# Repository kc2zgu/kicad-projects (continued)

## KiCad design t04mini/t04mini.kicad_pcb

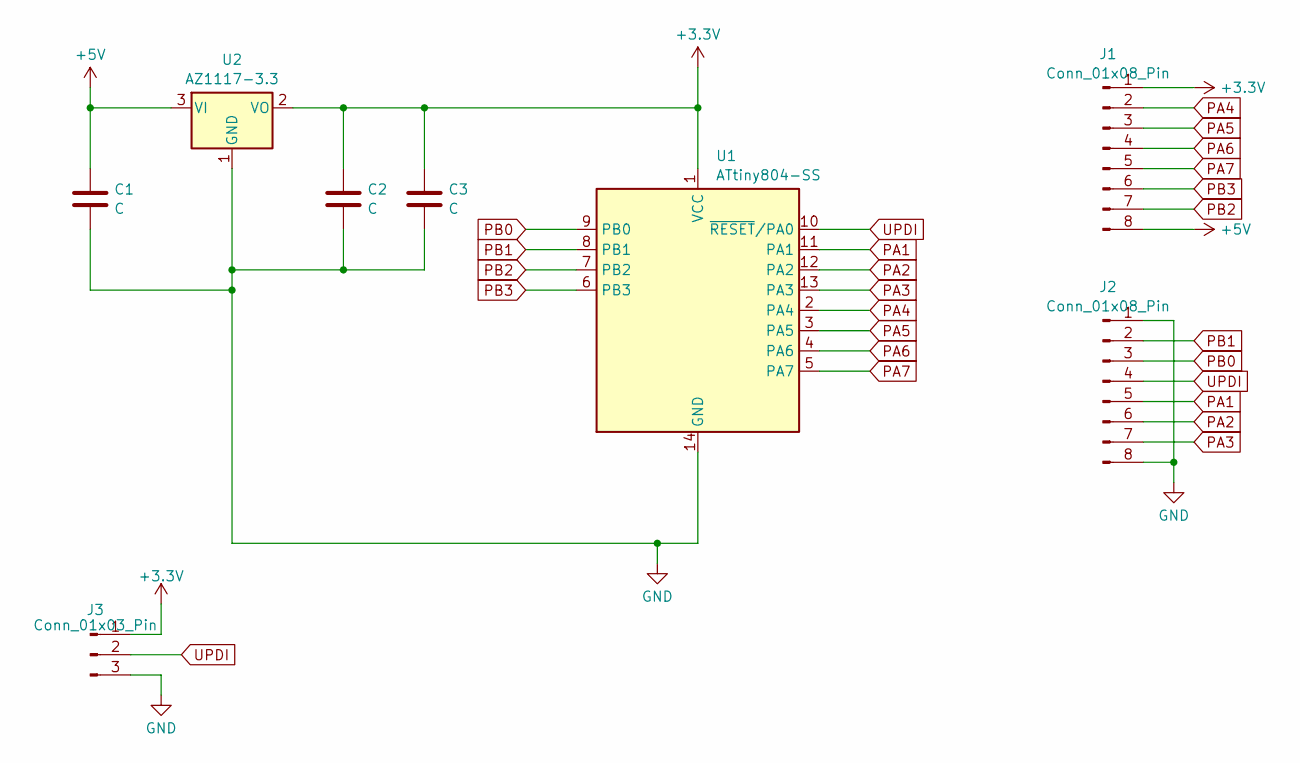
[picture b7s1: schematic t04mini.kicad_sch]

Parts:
C1, C2: C; C_1206_3216Metric
C3: C; C_0805_2012Metric_Pad1.18x1.45mm_HandSolder
J1, J2: Conn_01x08_Pin; PinHeader_1x08_P2.54mm_Vertical
J3: Conn_01x03_Pin; JST_ZH_B3B-ZR_1x03_P1.50mm_Vertical
U1: ATtiny804-SS; SOIC-14_3.9x8.7mm_P1.27mm
U2: AZ1117-3.3; SOT-89-3_Handsoldering

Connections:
+3.3V: C2.1, C3.1, J1.1, J3.1, U1.1 (VCC), U2.2 (VO)
+5V: C1.1, J1.8, U2.3 (VI)
GND: C1.2, C2.2, C3.2, J2.1, J2.8, J3.3, U1.14 (GND), U2.1 (GND)
PA1: J2.5, U1.11 (PA1)
PA2: J2.6, U1.12 (PA2)
PA3: J2.7, U1.13 (PA3)
PA4: J1.2, U1.2 (PA4)
PA5: J1.3, U1.3 (PA5)
PA6: J1.4, U1.4 (PA6)
PA7: J1.5, U1.5 (PA7)
PB0: J2.3, U1.9 (PB0)
PB1: J2.2, U1.8 (PB1)
PB2: J1.7, U1.7 (PB2)
PB3: J1.6, U1.6 (PB3)
UPDI: J2.4, J3.2, U1.10 (~RESET/PA0)

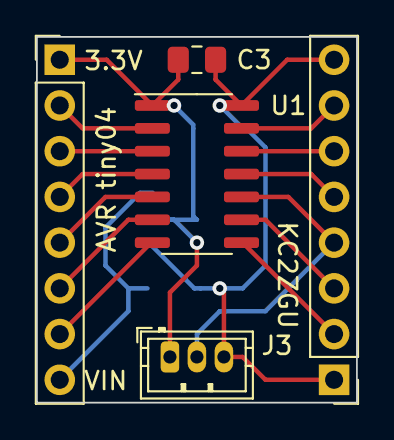
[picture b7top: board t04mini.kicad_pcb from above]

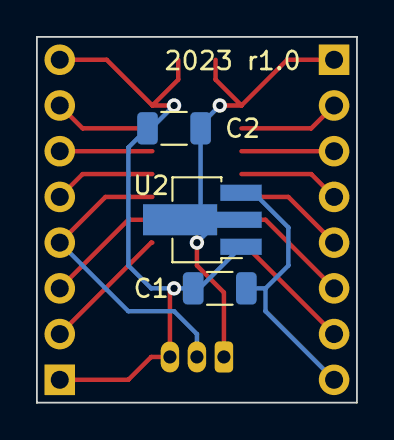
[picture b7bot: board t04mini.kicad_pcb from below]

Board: 2 copper layers, 17.8 x 20.3 mm, 8 parts (3 on the bottom side), 15 nets.

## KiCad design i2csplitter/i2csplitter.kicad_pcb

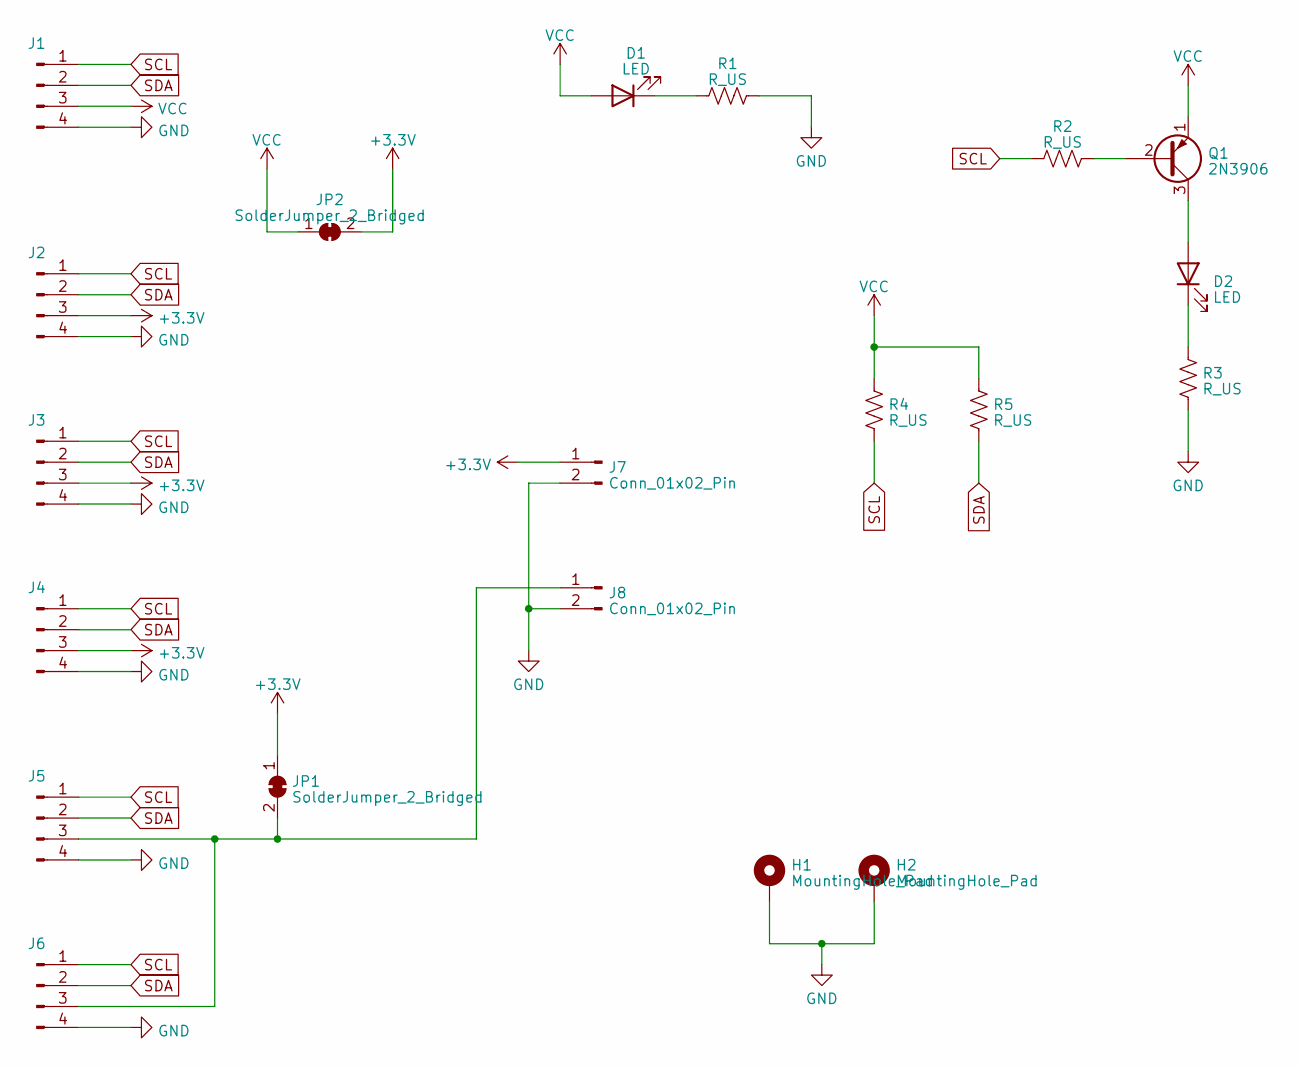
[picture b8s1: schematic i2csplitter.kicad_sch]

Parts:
D1, D2: LED; LED_D3.0mm
H1, H2: MountingHole_Pad; MountingHole_3.2mm_M3_DIN965_Pad
J1, J2, J3, J4, J5, J6: Conn_01x04_Male; JST_PH_B4B-PH-K_1x04_P2.00mm_Vertical
J7, J8: Conn_01x02_Pin; JST_PH_B2B-PH-K_1x02_P2.00mm_Vertical
JP1, JP2: SolderJumper_2_Bridged; SolderJumper-2_P1.3mm_Bridged_Pad1.0x1.5mm
Q1: 2N3906; TO-92_Inline
R1, R2, R3, R4, R5: R_US; R_0805_2012Metric_Pad1.20x1.40mm_HandSolder

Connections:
+3.3V: J2.3, J3.3, J4.3, J7.1, JP1.1 (A), JP2.2 (B)
GND: H1.1, H2.1, J1.4, J2.4, J3.4, J4.4, J5.4, J6.4, J7.2, J8.2, R1.2, R3.1
unnamed: D1.1 (K), R1.1
unnamed: D2.2 (A), Q1.3 (C)
unnamed: D2.1 (K), R3.2
unnamed: J5.3, J6.3, J8.1, JP1.2 (B)
unnamed: Q1.2 (B), R2.2
SCL: J1.1, J2.1, J3.1, J4.1, J5.1, J6.1, R2.1, R4.1
SDA: J1.2, J2.2, J3.2, J4.2, J5.2, J6.2, R5.1
VCC: D1.2 (A), J1.3, JP2.1 (A), Q1.1 (E), R4.2, R5.2

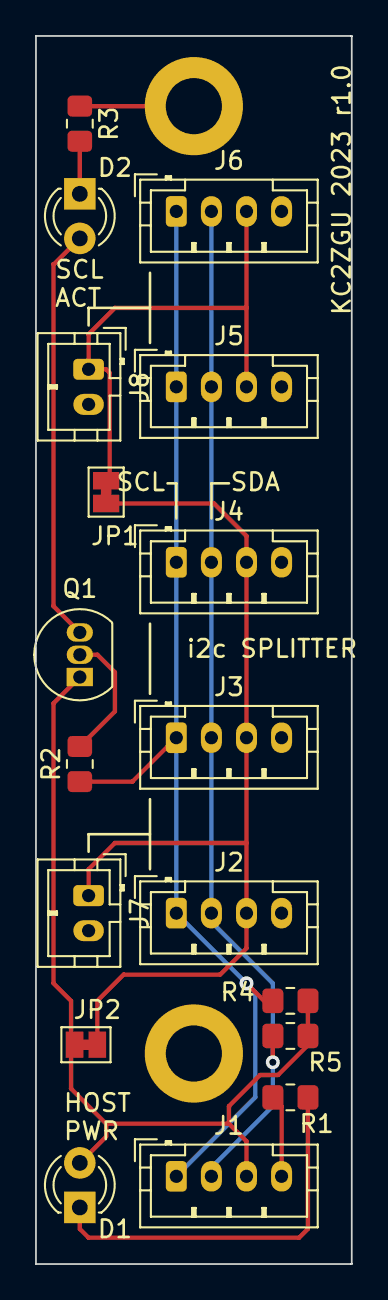
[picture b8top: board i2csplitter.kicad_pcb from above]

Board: 2 copper layers, 18.0 x 70.0 mm, 20 parts (0 on the bottom side), 10 nets.

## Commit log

2024-04-26 [old] mpio8: 8-channel IO board
2024-04-26 [old] hvac-r: relay board for HVAC control
2024-04-26 [old] led-mc-50x16: LED board (metal core design)
2024-04-26 [old] miniald: mini automated light driver (r1.0 fab snapshot)
2024-04-26 [old] mcumod-carrier-breakout: brreakout board for MCUmod
2024-04-26 [old] mcumod-at6: MCUmod for attiny06/16 family
2024-04-26 [old] smartpir: microcontroller-based PIR light driver
2024-04-26 [old] miniald: r1.1 (new UPDI header, change power rails)
2024-04-26 [old] mcumod-am8: MCUmod for atmega08 family
2024-04-26 [old] usbio: USB UART/I2C/ADC board with MCP2221A
2024-04-26 [old] i2csplitter: STEMMA I2C splitter/distribution board
2024-04-26 rpec: Raspberry Pi Essential Connectivity hat (r1.0 fab snapshot)
2024-04-26 [old] t04mini: attiny04/14 minimal breakout board
2024-04-26 rpec: schematic cosmetic fixes
2024-05-05 rpec: r1.1 (WIP)
    - Add Pi 5-compatible fan header
    - Move RTC components and use SMD crystal
2024-05-05 mpio8: r1.1
    - fix I2C connector pinout
    - DIP switch for address pins
2024-05-05 toob-hub: tiny OOB management hub (WIP)
2024-05-06 la-passthru: logic analyzer passthrough adapter
2024-05-06 add .gitignore
2024-05-06 add symbol library
2024-05-08 rpec: r1.1
    - Connect Pi 5 fan header
    - RTC voltage header
    - Header for Alternate ADC 1/2 inputs
2024-05-08 toob-hub r1.0
2024-05-17 mpio8: schematic PDF
2024-05-17 toob-pc: tiny OOB PC motherboard adapter
2024-05-17 mcp3426-breakout: breakout board for MCP3426 ADC
